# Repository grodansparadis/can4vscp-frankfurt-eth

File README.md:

<h1>CAN4VSCP Frankfurt Eth (PoE)</h1>

This work is based on original work done [here](https://github.com/nuclearcat/ESP32ETH). 

**Frankfurt Eth** is a tcp/ip and MQTT CAN4VSCP gateway. The module is available in two versions. One without PoE and and one with PoE.

The module is plug and play. Just connect to a CAN4VSCP system and go to work. You can connect to the module using [VSCP tcp/ip link protocol](https://grodansparadis.github.io/vscp-doc-spec/#/./vscp_tcpiplink) or set it up to talk to a MQTT broker of choice.

Note that this is **not** a CAN <-> tcp/ip (or MQTT) gateway as it only speaks [VSCP](https://grodansparadis.github.io/vscp-doc-spec). It is possible though to load firmware into it to create a standard CAN (not CAN FD) <-> tcp/ip gateway. 

The project uses an ESP32 Wroom module. It utilize Ethernet instead of Wifi/Bluetooth. Ethernet interface is provided with a LAN8720A and CAN is provided by the ESP32 support for TWAI. The module is powered from the [CAN4VSCP bus](https://grodansparadis.github.io/vscp-doc-spec/#/./vscp_over_can_can4vscp) (or PoE).  When powered from PoE the module can provide power for other CAN4VSCP modules. CAN4VSCP power is in the range +9V - 28V.

The intended use is to connect a remote CAN4VSCP bus to a central system or to connect two or more CAN4VSCP networks together. 

If Wifi is required instead of Ethernet the [CAN4VSCP Frankfurt Wifi module](https://github.com/grodansparadis/can4vscp-frankfurt-wifi) is available that can do that.

Prototype PCB's for this project has been sponsored by [PCBWay](https://www.pcbway.com/). We can really recommend this service if you need high quality PCB's. 

## Schema

### Standard version

### PoE version

## Standard version

## PoE Version

<hr>
Please support the <a href="http://www.vscp.org">VSCP development</a>. The best way to support the project is 
to buy something from the <a href="http://www.frogshop.se">FrogShop</a>. If you want to contribute money use the button
 at the end of the <a href="http://www.vscp.org">VSCP sites</a> start page.

Visit our <a href="http://www.vscp.org/wiki/doku.php/sponsors">sponsor page</a> for all options.

<hr>

Part of the VSCP Project.

Copyright 2018-2026 © Åke Hedman, (Grodans Paradis AB)[https://www.grodansparadis.com]

<hr>

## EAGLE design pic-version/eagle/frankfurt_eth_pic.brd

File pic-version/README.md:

# Microchip PIC Version

This is an old version of this project that is no longer maintained.

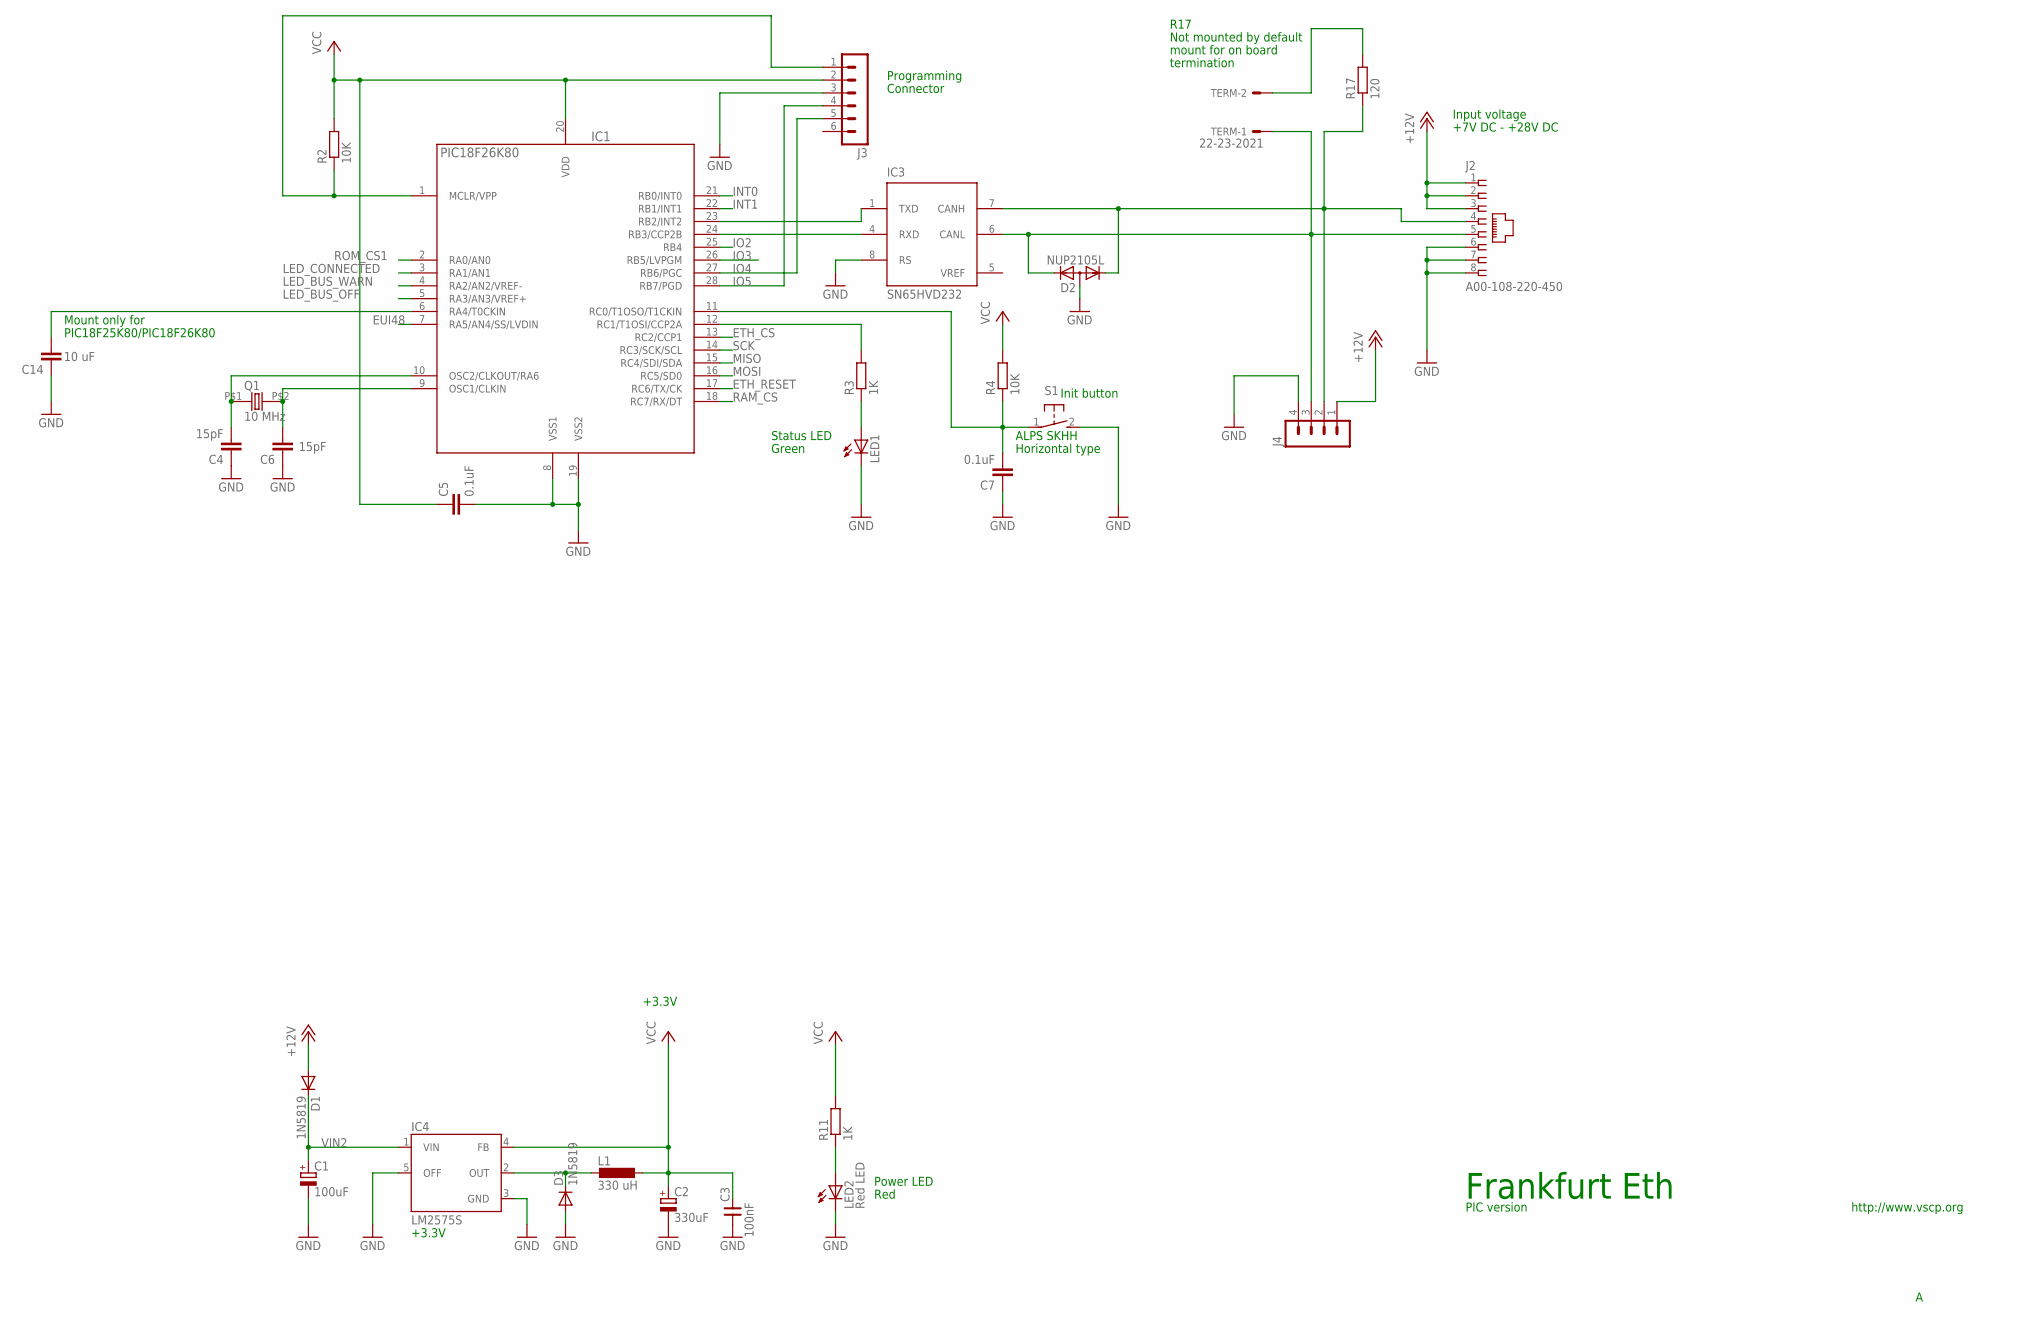
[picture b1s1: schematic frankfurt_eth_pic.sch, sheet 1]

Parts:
C1: 100uF; PANASONIC_D
C2: 330uF; PANASONIC_D
C3: 100nF; 0805
C4, C6: 15pF; C0805
C5, C7: 0.1uF; C0805
C14: 10 uF; C0805
D1, D3: 1N5819; SOD123
D2: NUP2105L; SOT23
IC1: PIC18F26K80; SO28
IC3: SN65HVD232; SO-08
IC4: LM2575S; TO263-5
J2: A00-108-220-450; RJ-45
J3: MA06-1
J4: MA04-1
L1: 330 uH; DO3316P
LED1: LEDCHIP-LED0805; CHIP-LED0805
LED2: Red LED; CHIP-LED0805
Q1: 10 MHz; 9C
R2, R4: 10K; R0805
R3, R11: 1K; R0805
R17: 120; R0805
S1: 31-XX; B3F-31XX
TERM: 22-23-2021

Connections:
+12V: D1.A, J2.1, J2.2, J2.3, J4.1
CANL: D2.2 (K2), IC3.6 (CANL), J2.5, J4.3, TERM.1
ETH_CS: IC1.13 (RC2/CCP1); also elsewhere on the board
ETH_RESET: IC1.17 (RC6/TX/CK); also elsewhere on the board
EUI48: IC1.7 (RA5/AN4/SS/LVDIN); also elsewhere on the board
GND: C1.-, C2.-, C3.1, C4.1, C5.2, C6.1, C7.1, C14.1, D2.3 (A), D3.A, IC1.8 (VSS1), IC1.19 (VSS2), IC3.2 (VSS), IC3.8 (RS), IC4.3 (GND), IC4.5 (OFF), J2.6, J2.7, J2.8, J3.3, J4.4, LED1.C, LED2.C, S1.2 (S); also elsewhere on the board
INT0: IC1.21 (RB0/INT0); also elsewhere on the board
INT1: IC1.22 (RB1/INT1); also elsewhere on the board
IO2: IC1.25 (RB4)
IO3: IC1.26 (RB5/LVPGM)
IO4: IC1.27 (RB6/PGC), J3.5
IO5: IC1.28 (RB7/PGD), J3.4
LED_BUS_OFF: IC1.5 (RA3/AN3/VREF+); also elsewhere on the board
LED_BUS_WARN: IC1.4 (RA2/AN2/VREF-); also elsewhere on the board
LED_CONNECTED: IC1.3 (RA1/AN1); also elsewhere on the board
MISO: IC1.15 (RC4/SDI/SDA); also elsewhere on the board
MOSI: IC1.16 (RC5/SD0); also elsewhere on the board
unnamed: D3.C, IC4.2 (OUT), L1.1
unnamed: C4.2, IC1.10 (OSC2/CLKOUT/RA6), Q1.P$1 (1)
unnamed: C14.2, IC1.6 (RA4/T0CKIN)
unnamed: IC1.12 (RC1/T1OSI/CCP2A), R3.2
unnamed: LED1.A, R3.1
unnamed: C7.2, IC1.11 (RC0/T1OSO/T1CKIN), R4.1, S1.1
unnamed: C6.2, IC1.9 (OSC1/CLKIN), Q1.P$2 (2)
unnamed: R17.2, TERM.2
unnamed: LED2.A, R11.1
unnamed: D2.1 (K1), IC3.7 (CANH), J2.4, J4.2, R17.1
RAM_CS: IC1.18 (RC7/RX/DT); also elsewhere on the board
RESET: IC1.1 (MCLR/VPP), J3.1, R2.1
ROM_CS1: IC1.2 (RA0/AN0); also elsewhere on the board
RXCAN: IC1.24 (RB3/CCP2B), IC3.4 (RXD)
SCK: IC1.14 (RC3/SCK/SCL); also elsewhere on the board
TXCAN: IC1.23 (RB2/INT2), IC3.1 (TXD)
VCC: C2.+, C3.2, C5.1, IC1.20 (VDD), IC3.3 (VDD), IC4.4 (FB), J3.2, L1.2, R2.2, R4.2, R11.2; also elsewhere on the board
VIN2: C1.+, D1.C, IC4.1 (VIN)
VREF: IC3.5 (VREF)

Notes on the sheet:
Init button
Status LED
Programming
Connector
ALPS SKHH
Horizontal type
Input voltage
+7V DC - +28V DC
Power LED
Red
Green
Mount only for
PIC18F25K80/PIC18F26K80
Not mounted by default
mount for on board
termination
R17
+3.3V
Frankfurt Eth
http://www.vscp.org
PIC version

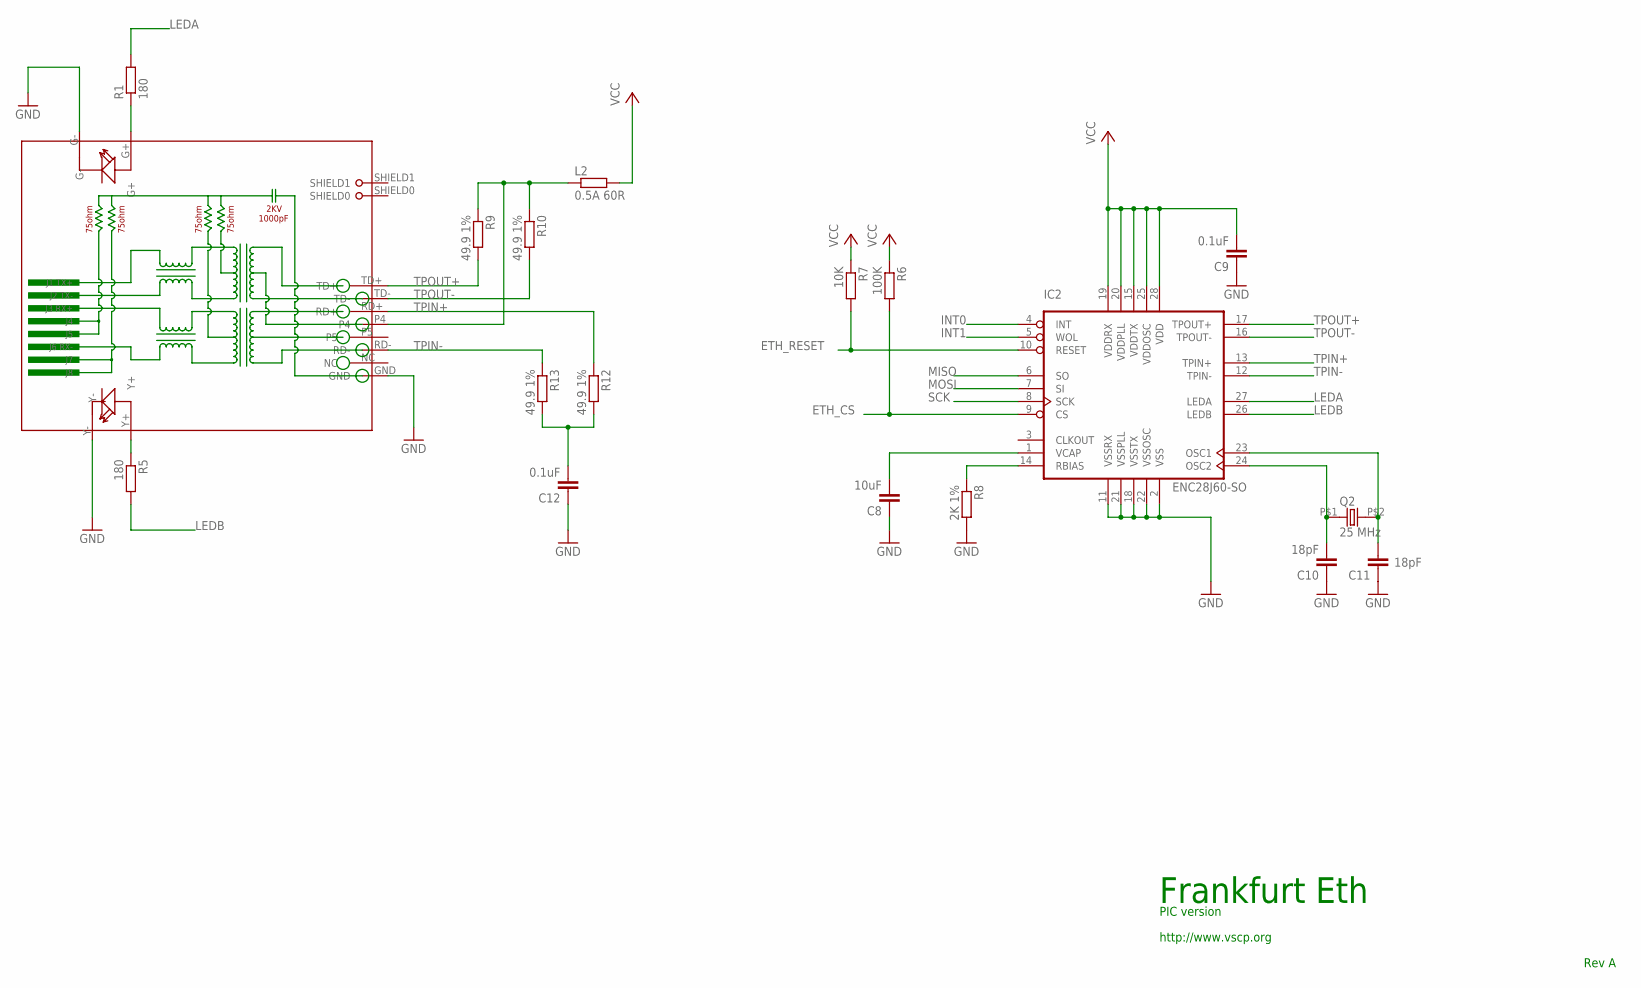
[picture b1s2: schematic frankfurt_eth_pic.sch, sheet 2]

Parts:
C8: 10uF; C0805
C9, C12: 0.1uF; C0805
C10, C11: 18pF; C0805
IC2: ENC28J60-SO; SO28W
L2: 0.5A 60R; R0805
Q2: 25 MHz; 9C
R1, R5: 180; R0805
R6: 100K; R0805
R7: 10K; R0805
R8: 2K 1%; R0805
R9, R10, R12, R13: 49.9 1%; R0805
RJ1: HR911105A

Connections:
ETH_CS: IC2.9 (CS), R6.2; also elsewhere on the board
ETH_RESET: IC2.10 (RESET), R7.2; also elsewhere on the board
GND: C8.1, C9.1, C10.1, C11.1, C12.1, IC2.2 (VSS), IC2.11 (VSSRX), IC2.18 (VSSTX), IC2.21 (VSSPLL), IC2.22 (VSSOSC), R8.2, RJ1.G-, RJ1.GND, RJ1.Y-; also elsewhere on the board
INT0: IC2.4 (INT); also elsewhere on the board
INT1: IC2.5 (WOL); also elsewhere on the board
LEDA: IC2.27 (LEDA), R1.2
LEDB: IC2.26 (LEDB), R5.2
MISO: IC2.6 (SO); also elsewhere on the board
MOSI: IC2.7 (SI); also elsewhere on the board
unnamed: R1.1, RJ1.G+
unnamed: C8.2, IC2.1 (VCAP)
unnamed: R5.1, RJ1.Y+
unnamed: IC2.14 (RBIAS), R8.1
unnamed: C10.2, IC2.24 (OSC2), Q2.P$1 (1)
unnamed: C11.2, IC2.23 (OSC1), Q2.P$2 (2)
unnamed: C12.2, R12.2, R13.2
unnamed: L2.1, R9.1, R10.1, RJ1.P4
SCK: IC2.8 (SCK); also elsewhere on the board
TPIN+: IC2.13 (TPIN+), R12.1, RJ1.RD+
TPIN-: IC2.12 (TPIN-), R13.1, RJ1.RD-
TPOUT+: IC2.17 (TPOUT+), R9.2, RJ1.TD+
TPOUT-: IC2.16 (TPOUT-), R10.2, RJ1.TD-
VCC: C9.2, IC2.15 (VDDTX), IC2.19 (VDDRX), IC2.20 (VDDPLL), IC2.25 (VDDOSC), IC2.28 (VDD), L2.2, R6.1, R7.1; also elsewhere on the board

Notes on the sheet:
Rev A
Frankfurt Eth
http://www.vscp.org
PIC version

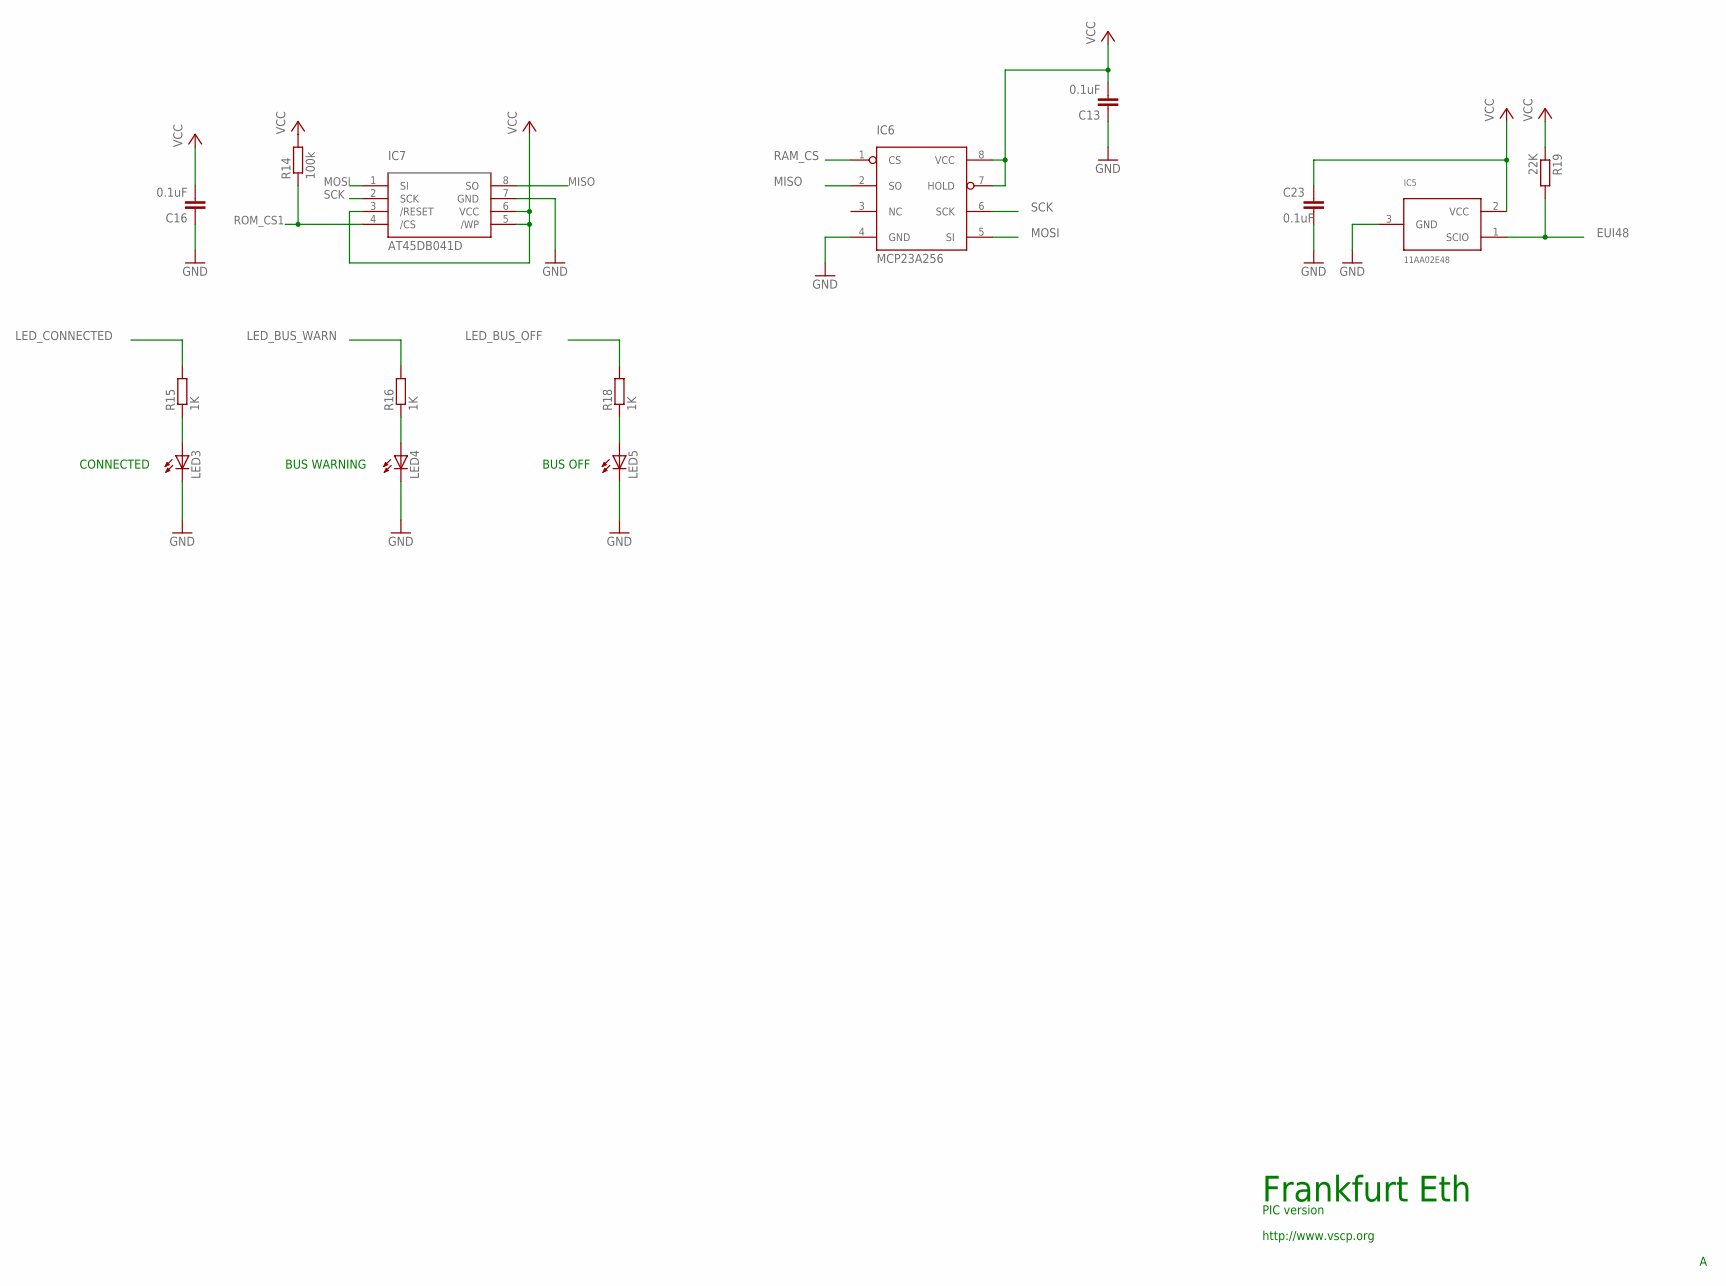
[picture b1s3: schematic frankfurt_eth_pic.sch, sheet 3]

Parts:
C13, C16, C23: 0.1uF; C0805
IC5: 11AA02E48; SOT23
IC6: MCP23A256; SO-8
IC7: AT45DB041D; SOP8W
LED3, LED4, LED5: LEDCHIP-LED0805; CHIP-LED0805
R14: 100k; M0805
R15, R16, R18: 1K; R0805
R19: 22K; M0805

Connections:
EUI48: IC5.1 (SCIO), R19.2; also elsewhere on the board
GND: C13.1, C16.1, C23.2, IC5.3 (GND), IC6.4 (GND), IC7.7 (GND), LED3.C, LED4.C, LED5.C; also elsewhere on the board
LED_BUS_OFF: R18.2; also elsewhere on the board
LED_BUS_WARN: R16.2; also elsewhere on the board
LED_CONNECTED: R15.2; also elsewhere on the board
MISO: IC6.2 (SO), IC7.8 (SO); also elsewhere on the board
MOSI: IC6.5 (SI), IC7.1 (SI); also elsewhere on the board
unnamed: LED3.A, R15.1
unnamed: LED4.A, R16.1
unnamed: LED5.A, R18.1
RAM_CS: IC6.1 (CS); also elsewhere on the board
ROM_CS1: IC7.4 (/CS), R14.1; also elsewhere on the board
SCK: IC6.6 (SCK), IC7.2 (SCK); also elsewhere on the board
VCC: C13.2, C16.2, C23.1, IC5.2 (VCC), IC6.7 (HOLD), IC6.8 (VCC), IC7.3 (/RESET), IC7.5 (/WP), IC7.6 (VCC), R14.2, R19.1; also elsewhere on the board

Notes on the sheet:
CONNECTED
BUS WARNING
BUS OFF
Frankfurt Eth
http://www.vscp.org
PIC version

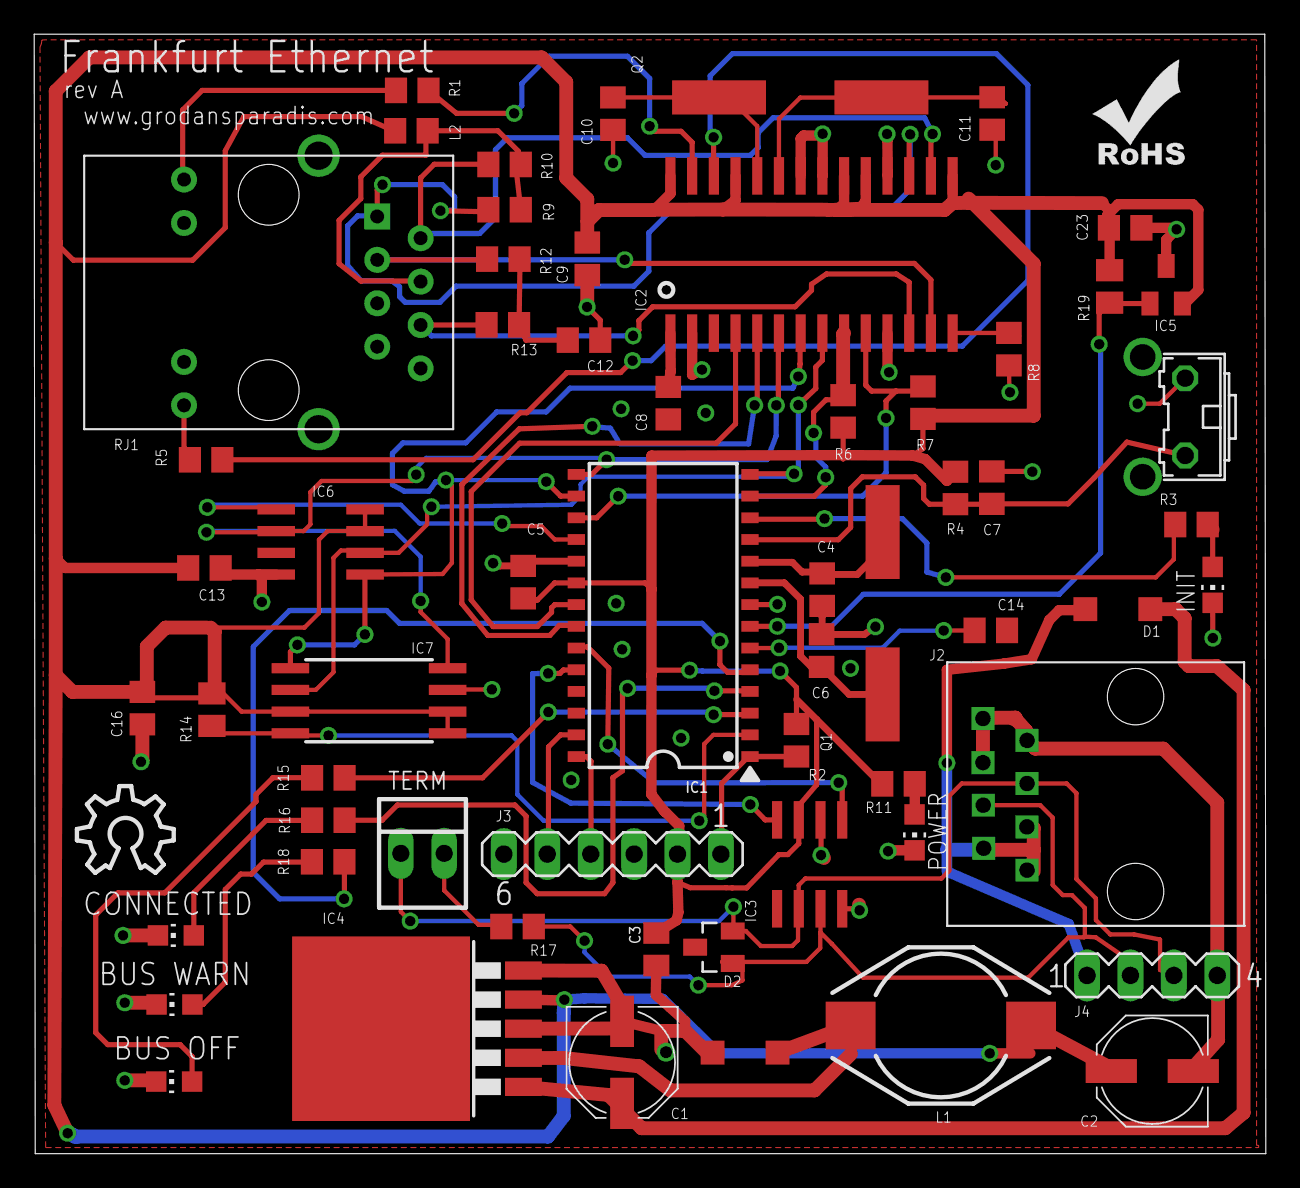
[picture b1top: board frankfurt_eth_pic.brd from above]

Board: 2 copper layers, 72.1 x 65.5 mm, 62 parts (0 on the bottom side), 50 nets.

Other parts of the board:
U$1: ROHS_SILK
U$2: OSHW_10X200_NOTEXT

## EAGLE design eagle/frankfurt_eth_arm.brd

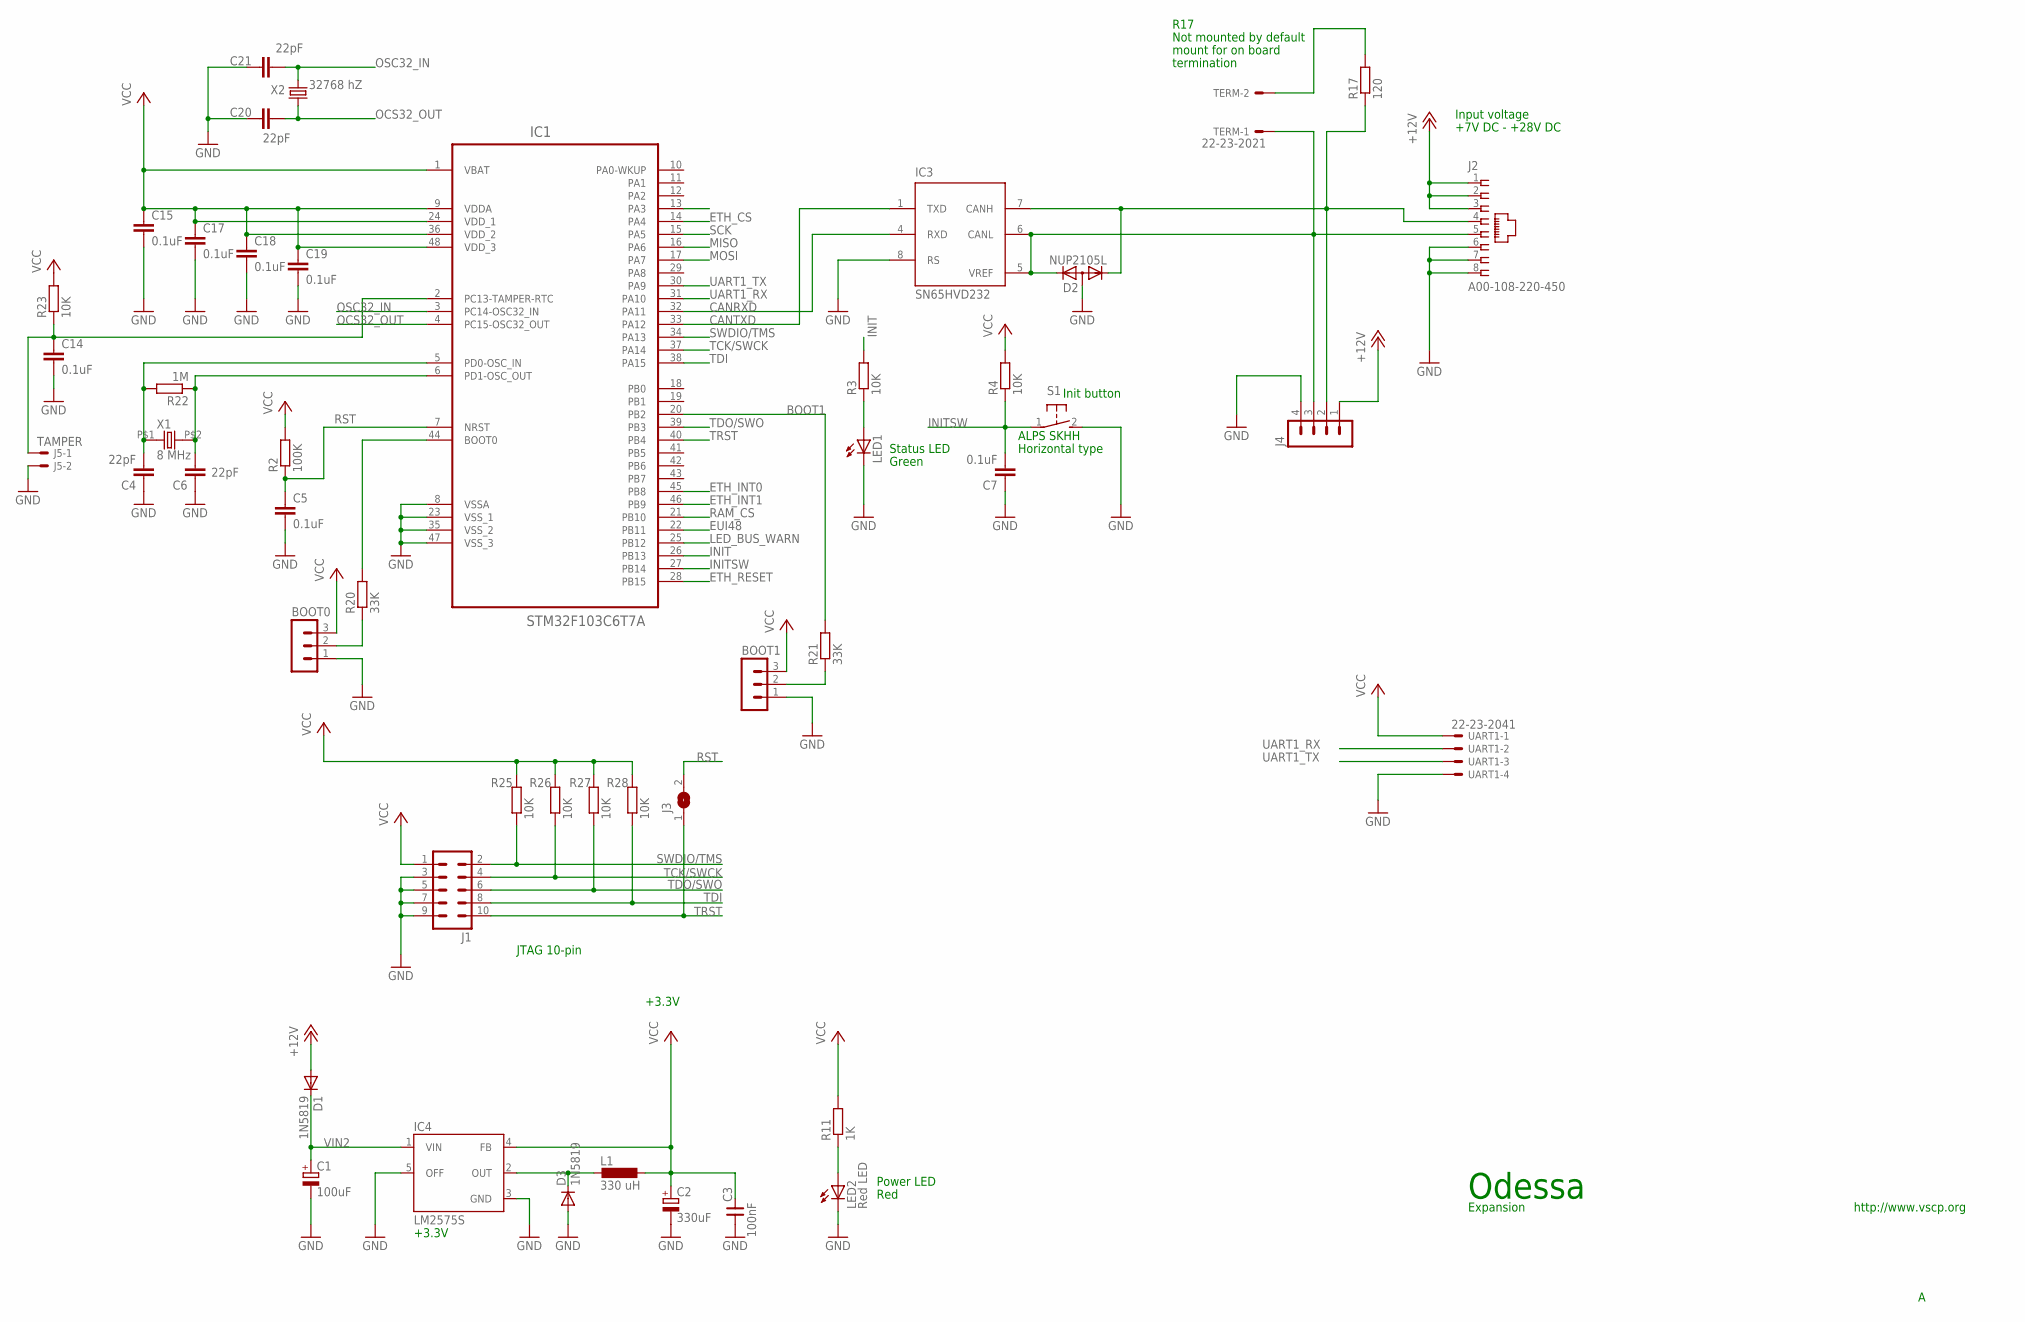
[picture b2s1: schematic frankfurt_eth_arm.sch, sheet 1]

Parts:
BOOT0, BOOT1: MA03-1
C1: 100uF; PANASONIC_D
C2: 330uF; PANASONIC_D
C3: 100nF; 0805
C4, C6, C20, C21: 22pF; C0805
C5, C7, C14, C15, C17, C18, C19: 0.1uF; C0805
D1, D3: 1N5819; SOD123
D2: NUP2105L; SOT23
IC1: STM32F103C6T7A; QFP50P900X900X160-48N
IC3: SN65HVD232; SO-08
IC4: LM2575S; TO263-5
J1: MA05-2
J2: A00-108-220-450; RJ-45
J3: SJ
J4: MA04-1
J5: TAMPER; 22-23-2021
L1: 330 uH; DO3316P
LED1: LEDCHIP-LED0805; CHIP-LED0805
LED2: Red LED; CHIP-LED0805
R2: 100K; R0805
R3, R4, R23, R25, R26, R27, R28: 10K; R0805
R11: 1K; R0805
R17: 120; R0805
R20, R21: 33K; R0805
R22: 1M; R0805
S1: 31-XX; B3F-31XX
TERM: 22-23-2021
UART1: 22-23-2041
X1: 8 MHz; 9C
X2: 32768 hZ; TC26H

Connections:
+12V: D1.A, J2.1, J2.2, J2.3, J4.1
BOOT0: IC1.44 (BOOT0), R20.2
BOOT1: IC1.20 (PB2), R21.2
CANL: D2.2 (K2), IC3.5 (VREF), IC3.6 (CANL), J2.5, J4.3, TERM.1
CANRXD: IC1.32 (PA11), IC3.4 (RXD)
CANTXD: IC1.33 (PA12), IC3.1 (TXD)
ETH_CS: IC1.14 (PA4); also elsewhere on the board
ETH_INT0: IC1.45 (PB8); also elsewhere on the board
ETH_INT1: IC1.46 (PB9); also elsewhere on the board
ETH_RESET: IC1.28 (PB15); also elsewhere on the board
EUI48: IC1.22 (PB11); also elsewhere on the board
GND: BOOT0.1, BOOT1.1, C1.-, C2.-, C3.1, C4.1, C5.2, C6.1, C7.1, C14.2, C15.2, C17.2, C18.2, C19.2, C20.1, C21.1, D2.3 (A), D3.A, IC1.8 (VSSA), IC1.23 (VSS_1), IC1.35 (VSS_2), IC1.47 (VSS_3), IC3.2 (VSS), IC3.8 (RS), IC4.3 (GND), IC4.5 (OFF), J1.3, J1.5, J1.7, J1.9, J2.6, J2.7, J2.8, J4.4, J5.2, LED1.C, LED2.C, S1.2 (S), UART1.4; also elsewhere on the board
INIT: IC1.26 (PB13), R3.2
INITSW: C7.2, IC1.27 (PB14), R4.1, S1.1
LED_BUS_WARN: IC1.25 (PB12)
MISO: IC1.16 (PA6); also elsewhere on the board
MOSI: IC1.17 (PA7); also elsewhere on the board
unnamed: D3.C, IC4.2 (OUT), L1.1
unnamed: C4.2, IC1.5 (PD0-OSC_IN), R22.2, X1.P$1 (1)
unnamed: LED1.A, R3.1
unnamed: C6.2, IC1.6 (PD1-OSC_OUT), R22.1, X1.P$2 (2)
unnamed: R17.2, TERM.2
unnamed: LED2.A, R11.1
unnamed: D2.1 (K1), IC3.7 (CANH), J2.4, J4.2, R17.1
unnamed: C14.1, IC1.2 (PC13-TAMPER-RTC), J5.1, R23.1
OCS32_OUT: C20.2, IC1.4 (PC15-OSC32_OUT), X2.1
OSC32_IN: C21.2, IC1.3 (PC14-OSC32_IN), X2.2
RAM_CS: IC1.21 (PB10); also elsewhere on the board
ROM_CS1: IC1.13 (PA3); also elsewhere on the board
RST: C5.1, IC1.7 (NRST), J3.2, R2.1
SCK: IC1.15 (PA5); also elsewhere on the board
SWDIO/TMS: IC1.34 (PA13), J1.2, R25.1
TCK/SWCK: IC1.37 (PA14), J1.4, R26.1
TDI: IC1.38 (PA15), J1.8, R28.1
TDO/SWO: IC1.39 (PB3), J1.6, R27.1
TRST: IC1.40 (PB4), J1.10, J3.1
UART1_RX: IC1.31 (PA10), UART1.2
UART1_TX: IC1.30 (PA9), UART1.3
VCC: BOOT0.3, BOOT1.3, C2.+, C3.2, C15.1, C17.1, C18.1, C19.1, IC1.1 (VBAT), IC1.9 (VDDA), IC1.24 (VDD_1), IC1.36 (VDD_2), IC1.48 (VDD_3), IC3.3 (VDD), IC4.4 (FB), J1.1, L1.2, R2.2, R4.2, R11.2, R23.2, R25.2, R26.2, R27.2, R28.2, UART1.1; also elsewhere on the board
VIN2: C1.+, D1.C, IC4.1 (VIN)
_BOOT0: BOOT0.2, R20.1
_BOOT1: BOOT1.2, R21.1

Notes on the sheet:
Init button
Status LED
ALPS SKHH
Horizontal type
Odessa
http://www.vscp.org
Expansion
Input voltage
+7V DC - +28V DC
Power LED
Red
Green
Not mounted by default
mount for on board
termination
R17
+3.3V
JTAG 10-pin

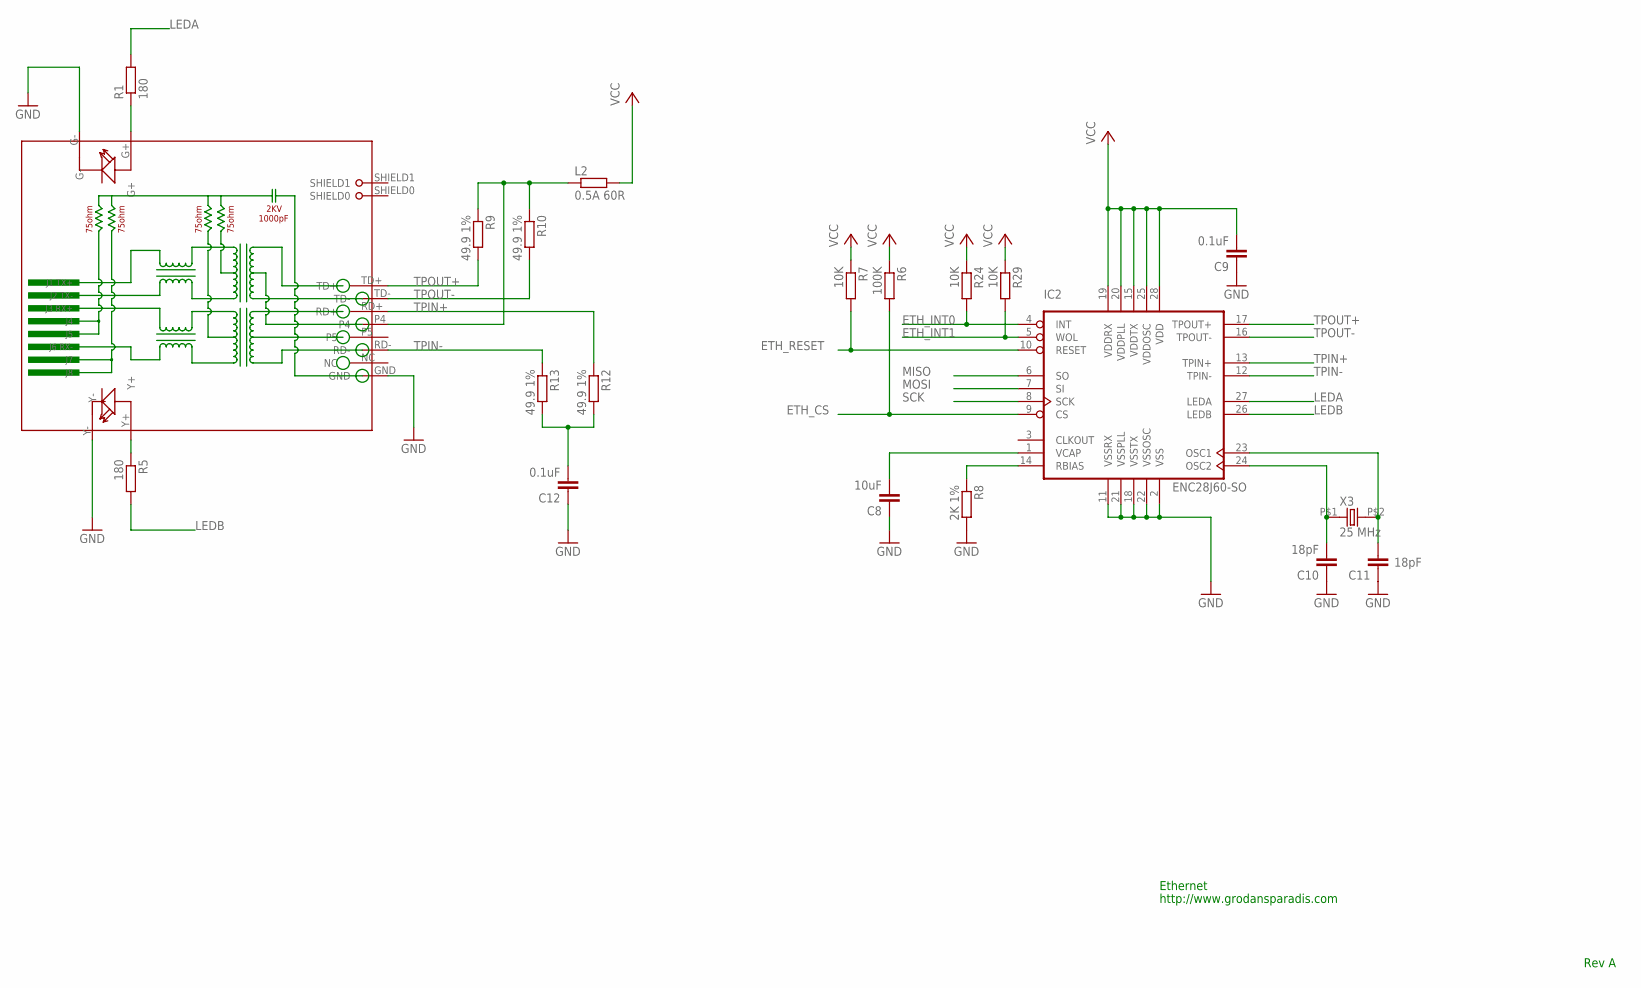
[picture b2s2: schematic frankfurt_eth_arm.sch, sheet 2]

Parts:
C8: 10uF; C0805
C9, C12: 0.1uF; C0805
C10, C11: 18pF; C0805
IC2: ENC28J60-SO; SO28W
L2: 0.5A 60R; R0805
R1, R5: 180; R0805
R6: 100K; R0805
R7, R24, R29: 10K; R0805
R8: 2K 1%; R0805
R9, R10, R12, R13: 49.9 1%; R0805
RJ1: HR911105A
X3: 25 MHz; 9C

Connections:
ETH_CS: IC2.9 (CS), R6.2; also elsewhere on the board
ETH_INT0: IC2.4 (INT), R24.2; also elsewhere on the board
ETH_INT1: IC2.5 (WOL), R29.2; also elsewhere on the board
ETH_RESET: IC2.10 (RESET), R7.2; also elsewhere on the board
GND: C8.1, C9.1, C10.1, C11.1, C12.1, IC2.2 (VSS), IC2.11 (VSSRX), IC2.18 (VSSTX), IC2.21 (VSSPLL), IC2.22 (VSSOSC), R8.2, RJ1.G-, RJ1.GND, RJ1.Y-; also elsewhere on the board
LEDA: IC2.27 (LEDA), R1.2
LEDB: IC2.26 (LEDB), R5.2
MISO: IC2.6 (SO); also elsewhere on the board
MOSI: IC2.7 (SI); also elsewhere on the board
unnamed: R1.1, RJ1.G+
unnamed: C8.2, IC2.1 (VCAP)
unnamed: R5.1, RJ1.Y+
unnamed: IC2.14 (RBIAS), R8.1
unnamed: C10.2, IC2.24 (OSC2), X3.P$1 (1)
unnamed: C11.2, IC2.23 (OSC1), X3.P$2 (2)
unnamed: C12.2, R12.2, R13.2
unnamed: L2.1, R9.1, R10.1, RJ1.P4
SCK: IC2.8 (SCK); also elsewhere on the board
TPIN+: IC2.13 (TPIN+), R12.1, RJ1.RD+
TPIN-: IC2.12 (TPIN-), R13.1, RJ1.RD-
TPOUT+: IC2.17 (TPOUT+), R9.2, RJ1.TD+
TPOUT-: IC2.16 (TPOUT-), R10.2, RJ1.TD-
VCC: C9.2, IC2.15 (VDDTX), IC2.19 (VDDRX), IC2.20 (VDDPLL), IC2.25 (VDDOSC), IC2.28 (VDD), L2.2, R6.1, R7.1, R24.1, R29.1; also elsewhere on the board

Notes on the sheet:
Ethernet
Rev A
http://www.grodansparadis.com

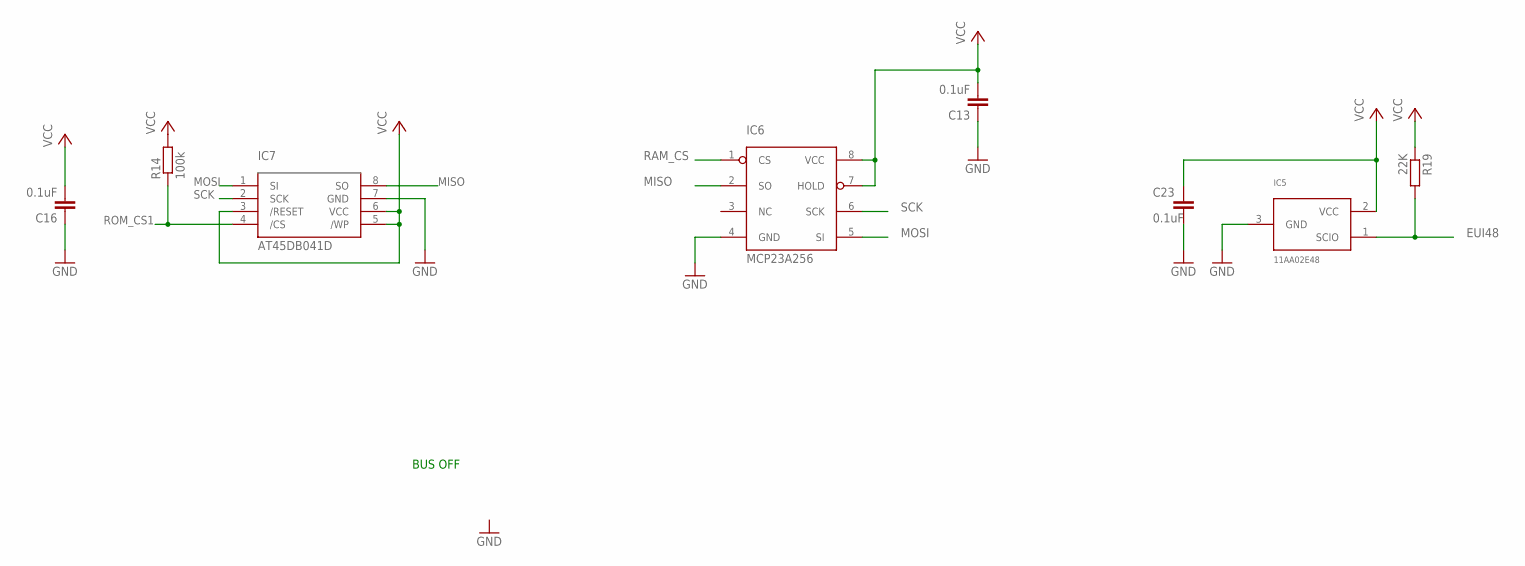
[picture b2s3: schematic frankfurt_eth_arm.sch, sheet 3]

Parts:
C13, C16, C23: 0.1uF; C0805
IC5: 11AA02E48; SOT23
IC6: MCP23A256; SO-8
IC7: AT45DB041D; SOP8W
R14: 100k; M0805
R19: 22K; M0805

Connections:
EUI48: IC5.1 (SCIO), R19.2; also elsewhere on the board
GND: C13.1, C16.1, C23.2, IC5.3 (GND), IC6.4 (GND), IC7.7 (GND); also elsewhere on the board
MISO: IC6.2 (SO), IC7.8 (SO); also elsewhere on the board
MOSI: IC6.5 (SI), IC7.1 (SI); also elsewhere on the board
RAM_CS: IC6.1 (CS); also elsewhere on the board
ROM_CS1: IC7.4 (/CS), R14.1; also elsewhere on the board
SCK: IC6.6 (SCK), IC7.2 (SCK); also elsewhere on the board
VCC: C13.2, C16.2, C23.1, IC5.2 (VCC), IC6.7 (HOLD), IC6.8 (VCC), IC7.3 (/RESET), IC7.5 (/WP), IC7.6 (VCC), R14.2, R19.1; also elsewhere on the board

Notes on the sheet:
BUS OFF

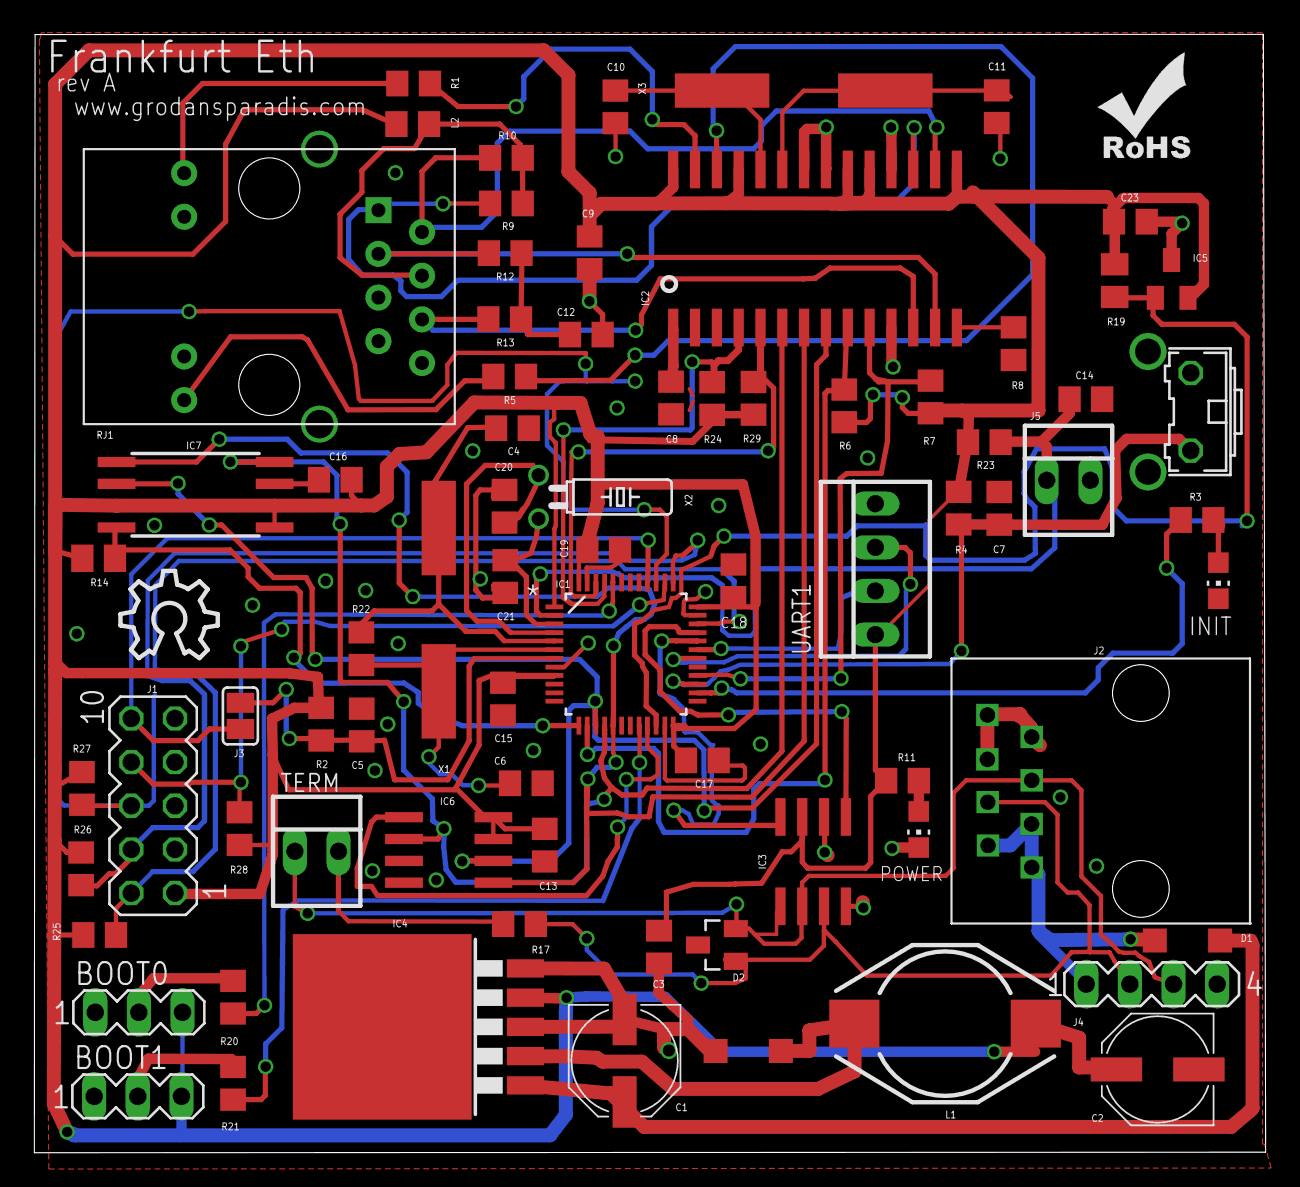
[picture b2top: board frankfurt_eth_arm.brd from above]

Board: 2 copper layers, 71.7 x 65.1 mm, 78 parts (0 on the bottom side), 55 nets.

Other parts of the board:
U$1: ROHS_SILK
U$2: OSHW_10X200_NOTEXT

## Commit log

2015-08-17 Initial check in after freedom day
2015-08-17 Changed license to Artistic License 3.0
2015-08-26 Added first version of hardware board
2015-08-26 Ignoring temp files
2015-08-26 Removed old folders
2015-08-28 Edit
2015-08-31 Started ARM version
2015-08-31 Routed
2015-09-01 Clean
2015-09-01 Removed extra status LED's
2015-09-01 edit text layer
2015-09-01 Renamed PIC version
2015-09-02 Added Gerbers
2015-09-02 Removed unused file
2015-09-02 Moved out R14 a bit
2015-09-02 Updated rev texts
2015-09-02 Added board and schema pictures
2015-09-15 Added some info
2015-09-15 Changed a link
2015-09-21 Increase width of vcc for uart connector
2015-09-25 New Gerbers
2015-10-20 Changed layer for info text on pic board
2015-11-13 Rearranged folders
2015-12-17 Updated readme and license
2016-04-04 Changed value of C14 to 10uF
2023-03-03 Added eps32 version
2023-03-06 ESP32 version 1 preliminary done
2023-03-06 Added history file
2023-03-06 Fixed README
2023-03-06 Added pdf schemas for poe version
2023-03-07 Added readme's
2023-03-07 Added link to pcbway
2023-03-07 Added pcbway logo
2023-03-07 Fixed spellig errors
2023-04-25 Added POE version
2025-09-19 Translated schemas to KiCad format
2025-09-19 Added som inital level II build code
2025-09-30 /home/akhe/development/VSCP/can4vscp-odessa/LICENSE
2026-01-28 Updated copyright year
2026-05-05 Rearranged
2026-05-05 Updated license to CERN
